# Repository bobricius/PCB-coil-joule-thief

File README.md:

# PCB coil joule thief

Hardware licensed under CERN OHL 1.2

Documentation licensed under CC-BY 4.0

Some measurements

Input voltage 1.5V

Startup voltage 0.5V

Frequency 260Khz

Input current 36mA

Output current 5mA through LED

Output voltage without load 20V

Project page https://hackaday.io/project/159611-pcb-coil-joule-thief

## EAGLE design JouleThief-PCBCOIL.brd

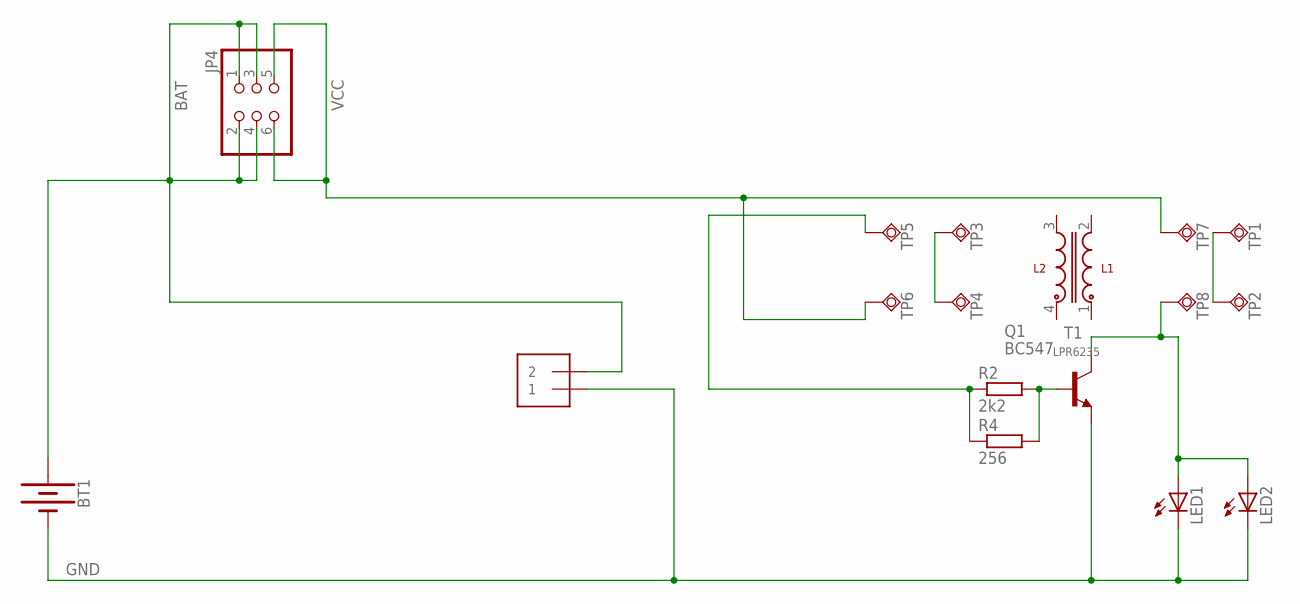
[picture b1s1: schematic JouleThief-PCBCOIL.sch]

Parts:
BT1: BATTERY-AAA_KIT; BATTERY-AAA-KIT
J1: 1X2-3.5MM
JP4: PINHD-2X3; 2X03
LED1: LEDKA-3528ASYC; KA-3528ASYC
LED2: LED5MM
Q1: BC547; TO92
R2: 2k2; 0204/5@1
R4: 256; R0603
T1: LPR6235
TP1, TP2, TP3, TP4, TP5, TP6, TP7, TP8: TPSQTP07R; TP07R

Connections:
BAT: BT1.PWR@1 (+), J1.2, JP4.1, JP4.2, JP4.3, JP4.4
GND: BT1.GND@1 (-), J1.1, LED1.C, LED2.K (C), Q1.1 (E)
unnamed: R2.1, R4.1, TP5.TP
unnamed: Q1.2 (B), R2.2, R4.2
unnamed: LED1.A, LED2.A, Q1.3 (C), TP8.TP
unnamed: TP3.TP, TP4.TP
unnamed: TP1.TP, TP2.TP
VCC: JP4.5, JP4.6, TP6.TP, TP7.TP

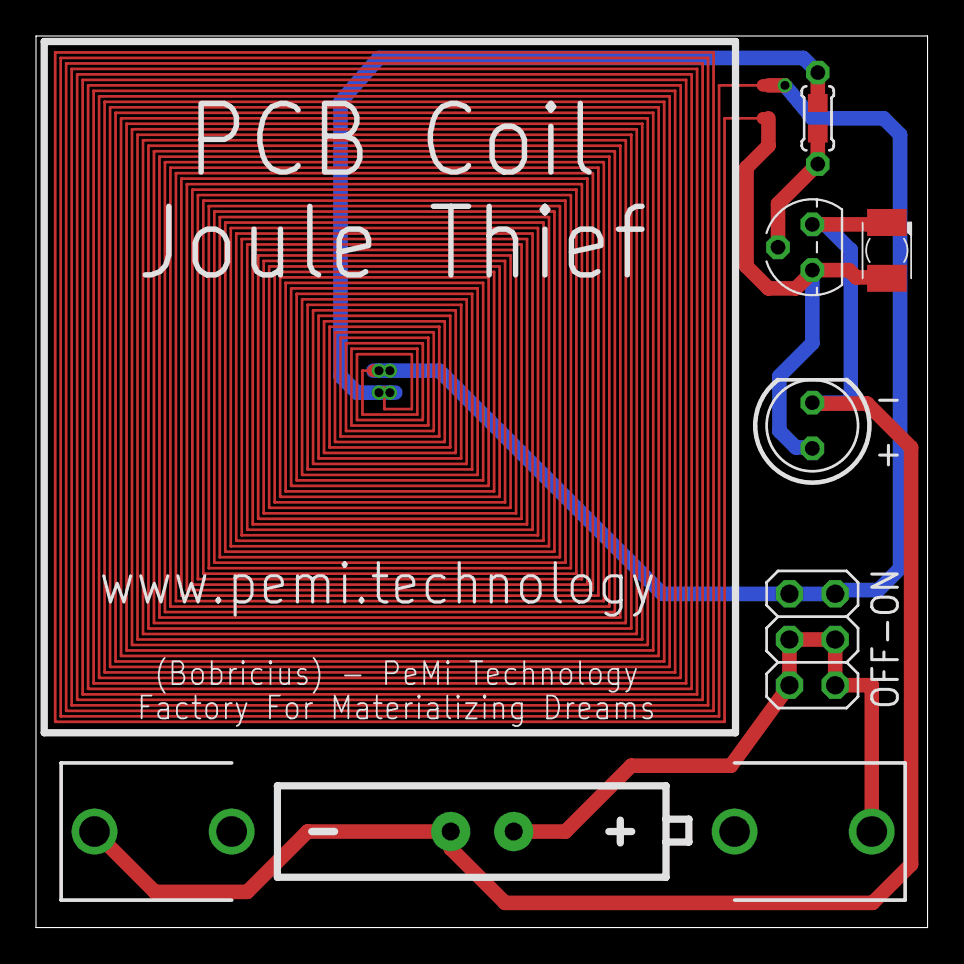
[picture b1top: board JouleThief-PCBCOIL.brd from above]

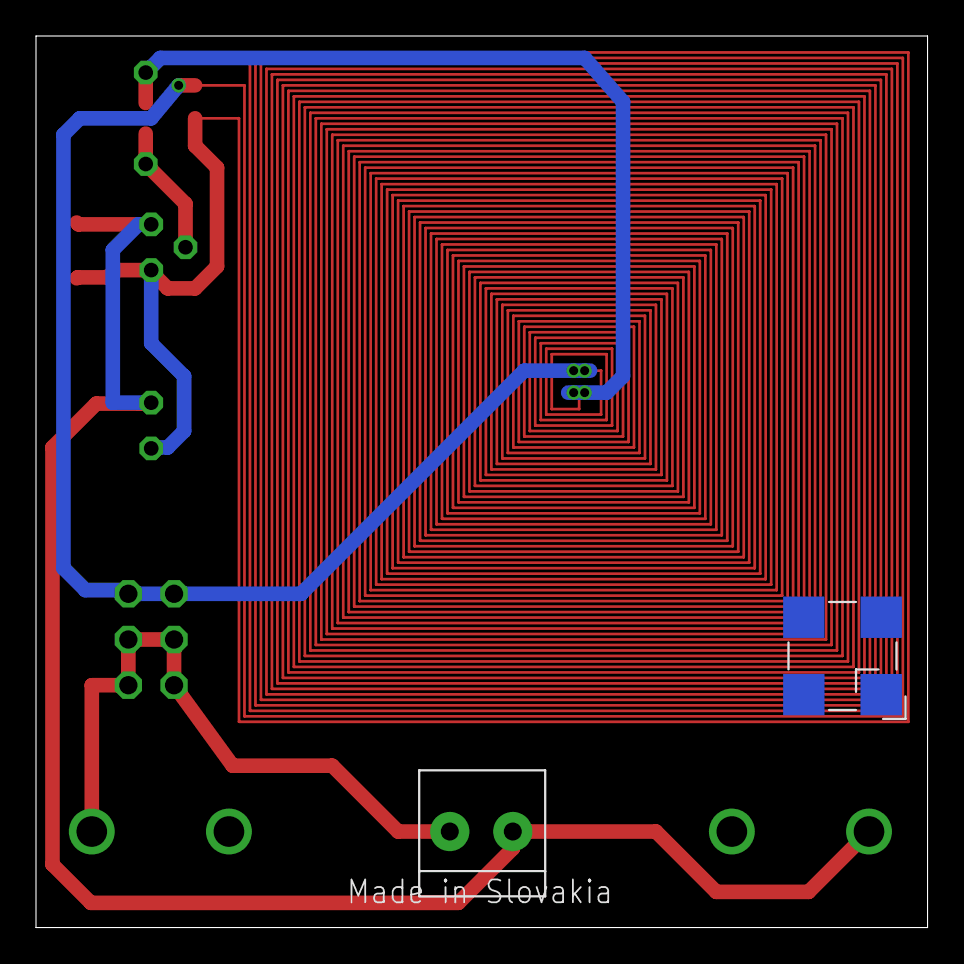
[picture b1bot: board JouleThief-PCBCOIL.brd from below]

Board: 2 copper layers, 49.5 x 49.5 mm, 17 parts (4 on the bottom side), 8 nets.

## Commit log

2018-07-15 First upload
    This year is Year of PCB coils ;-)
    2x 29turns 6/6mil

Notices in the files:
parts and their libraries:
SparkFun-Batteries: Licensing: Creative Commons ShareAlike 4.0 International - https://creativecommons.org/licenses/by-sa/4.0
